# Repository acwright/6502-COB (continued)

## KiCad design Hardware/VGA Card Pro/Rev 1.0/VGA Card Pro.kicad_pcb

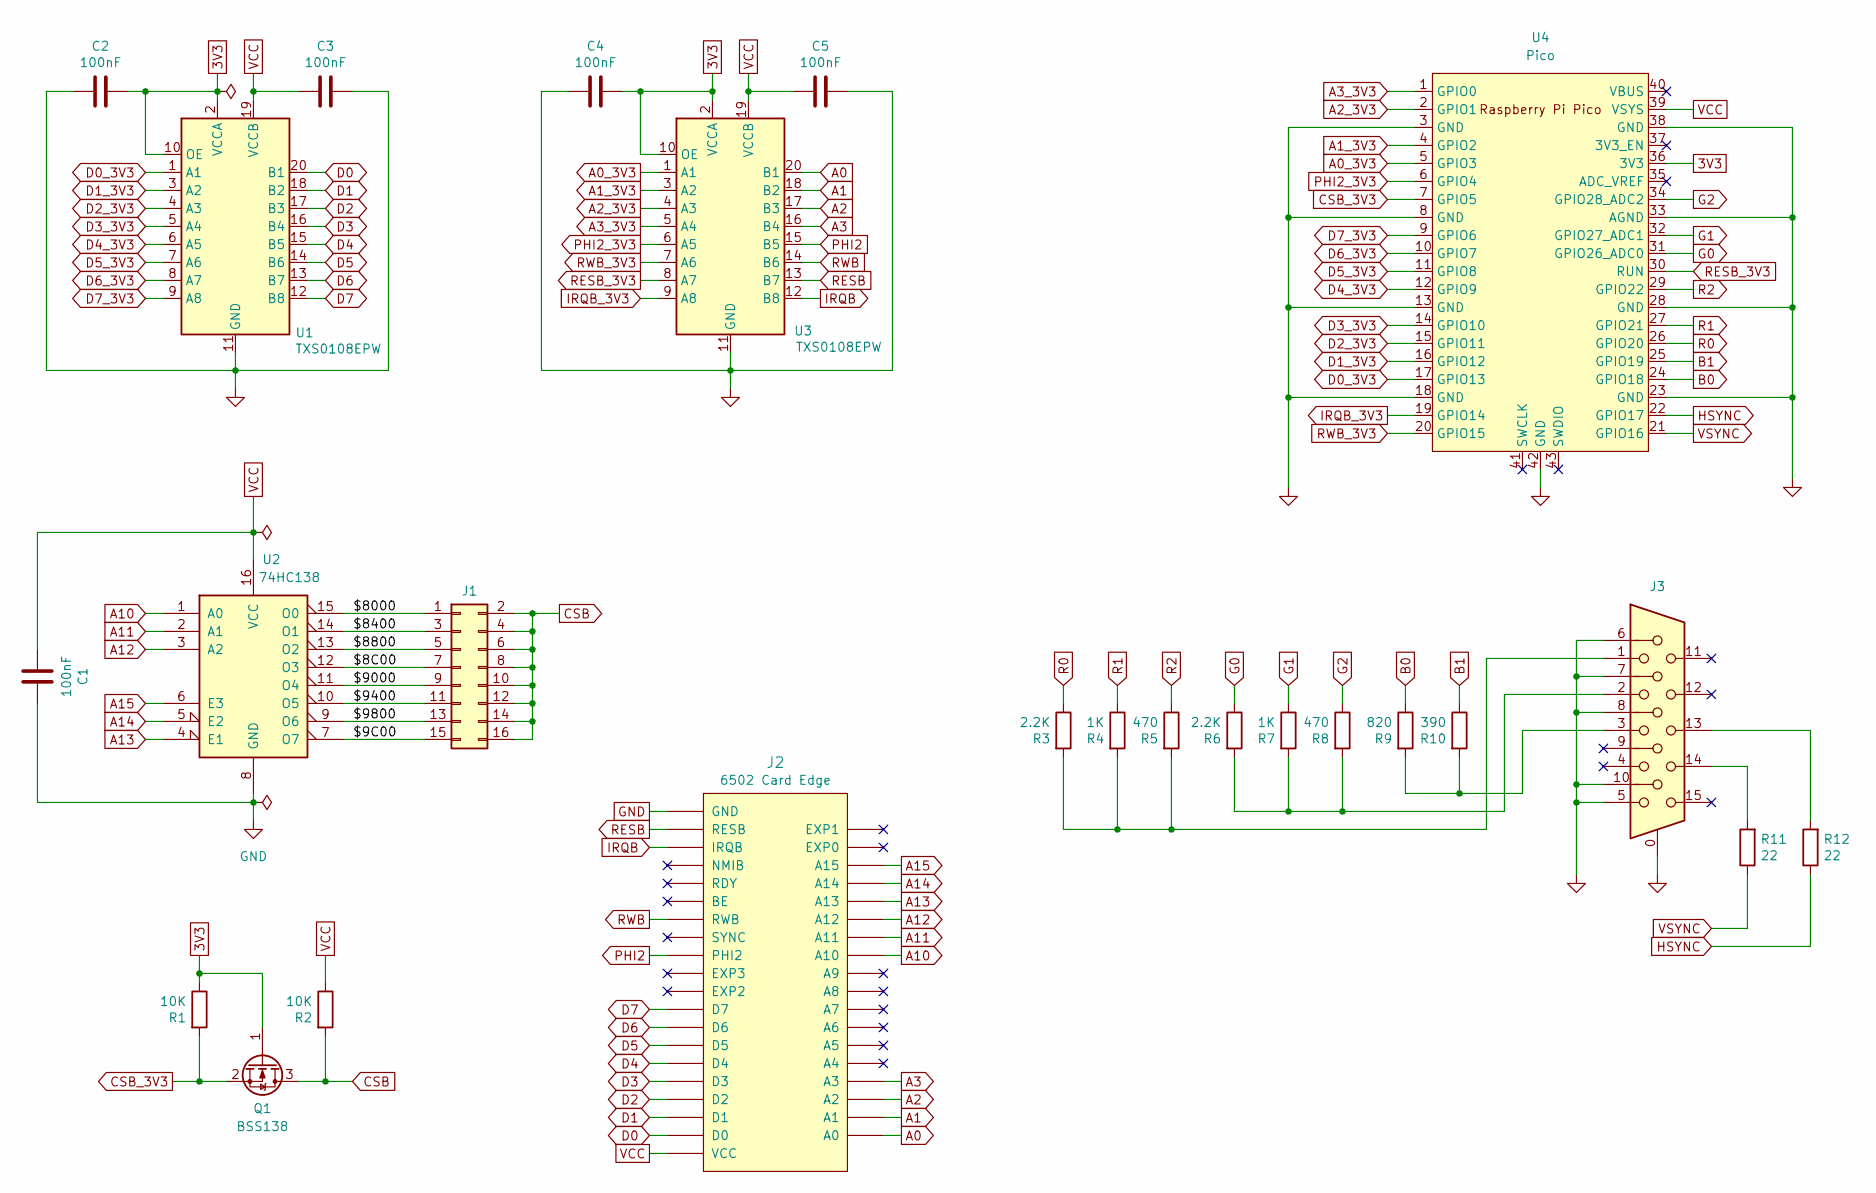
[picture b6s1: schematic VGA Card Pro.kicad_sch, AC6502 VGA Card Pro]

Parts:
C1, C2, C3, C4, C5: 100nF; C_0805_2012Metric; LCSC C49678
J1: Conn_02x08_Odd_Even; PinHeader_2x08_P2.54mm_Vertical; Digikey S2011EC-40-ND
J2: 6502 Card Edge
J3: DE15_Receptacle_HighDensity_MountingHoles; DSUB-15-HD_Female_Horizontal_P2.29x1.98mm_EdgePinOffset3.03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; Digikey 609-5181-ND
Q1: BSS138; SOT-23; LCSC C78284
R1, R2: 10K; R_0805_2012Metric; LCSC C17414
R3, R6: 2.2K; R_0805_2012Metric; LCSC C17520
R4, R7: 1K; R_0805_2012Metric; LCSC C17513
R5, R8: 470; R_0805_2012Metric; LCSC C17710
R9: 820; R_0805_2012Metric; LCSC C17837
R10: 390; R_0805_2012Metric; LCSC C17655
R11, R12: 22; R_0805_2012Metric; LCSC C17561
U1, U3: TXS0108EPW; TSSOP-20_4.4x6.5mm_P0.65mm; LCSC C17206
U2: 74HC138; SOIC-16_3.9x9.9mm_P1.27mm; LCSC C5602
U4: Pico; Raspberry Pi Pico; Digikey 2648-SC0915CT-ND

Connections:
3V3: C2.1, C4.1, Q1.1 (G), R1.1, U1.2 (VCCA), U1.10 (OE), U3.2 (VCCA), U3.10 (OE), U4.36 (3V3)
/$8C00: J1.7, U2.12 (O3)
/$9C00: J1.15, U2.7 (O7)
/$8000: J1.1, U2.15 (O0)
/$8400: J1.3, U2.14 (O1)
/$8800: J1.5, U2.13 (O2)
/$9000: J1.9, U2.11 (O4)
/$9400: J1.11, U2.10 (O5)
/$9800: J1.13, U2.9 (O6)
A0: J2.A0, U3.20 (B1)
A0_3V3: U3.1 (A1), U4.5 (GPIO3)
A1: J2.A1, U3.18 (B2)
A1_3V3: U3.3 (A2), U4.4 (GPIO2)
A2: J2.A2, U3.17 (B3)
A2_3V3: U3.4 (A3), U4.2 (GPIO1)
A3: J2.A3, U3.16 (B4)
A3_3V3: U3.5 (A4), U4.1 (GPIO0)
A10: J2.A10, U2.1 (A0)
A11: J2.A11, U2.2 (A1)
A12: J2.A12, U2.3 (A2)
A13: J2.A13, U2.4 (E1)
A14: J2.A14, U2.5 (E2)
A15: J2.A15, U2.6 (E3)
B0: R9.1, U4.24 (GPIO18)
B1: R10.1, U4.25 (GPIO19)
CSB: J1.2, J1.4, J1.6, J1.8, J1.10, J1.12, J1.14, J1.16, Q1.3 (D), R2.2
CSB_3V3: Q1.2 (S), R1.2, U4.7 (GPIO5)
D0: J2.D0, U1.20 (B1)
D0_3V3: U1.1 (A1), U4.17 (GPIO13)
D1: J2.D1, U1.18 (B2)
D1_3V3: U1.3 (A2), U4.16 (GPIO12)
D2: J2.D2, U1.17 (B3)
D2_3V3: U1.4 (A3), U4.15 (GPIO11)
D3: J2.D3, U1.16 (B4)
D3_3V3: U1.5 (A4), U4.14 (GPIO10)
D4: J2.D4, U1.15 (B5)
D4_3V3: U1.6 (A5), U4.12 (GPIO9)
D5: J2.D5, U1.14 (B6)
D5_3V3: U1.7 (A6), U4.11 (GPIO8)
D6: J2.D6, U1.13 (B7)
D6_3V3: U1.8 (A7), U4.10 (GPIO7)
D7: J2.D7, U1.12 (B8)
D7_3V3: U1.9 (A8), U4.9 (GPIO6)
G0: R6.1, U4.31 (GPIO26_ADC0)
G1: R7.1, U4.32 (GPIO27_ADC1)
G2: R8.1, U4.34 (GPIO28_ADC2)
GND: C1.2, C2.2, C3.1, C4.2, C5.1, J2.GND, J3.0, J3.5, J3.6, J3.7, J3.8, J3.10, U1.11 (GND), U2.8 (GND), U3.11 (GND), U4.3 (GND), U4.8 (GND), U4.13 (GND), U4.18 (GND), U4.23 (GND), U4.28 (GND), U4.33 (AGND), U4.38 (GND), U4.42 (GND)
HSYNC: R12.1, U4.22 (GPIO17)
IRQB: J2.IRQB, U3.12 (B8)
IRQB_3V3: U3.9 (A8), U4.19 (GPIO14)
unnamed: J3.1, R3.2, R4.2, R5.2
unnamed: J3.2, R6.2, R7.2, R8.2
unnamed: J3.3, R9.2, R10.2
unnamed: J3.13, R12.2
unnamed: J3.14, R11.2
PHI2: J2.PHI2, U3.15 (B5)
PHI2_3V3: U3.6 (A5), U4.6 (GPIO4)
R0: R3.1, U4.26 (GPIO20)
R1: R4.1, U4.27 (GPIO21)
R2: R5.1, U4.29 (GPIO22)
RESB: J2.RESB, U3.13 (B7)
RESB_3V3: U3.8 (A7), U4.30 (RUN)
RWB: J2.RWB, U3.14 (B6)
RWB_3V3: U3.7 (A6), U4.20 (GPIO15)
VCC: C1.1, C3.2, C5.2, J2.VCC, R2.1, U1.19 (VCCB), U2.16 (VCC), U3.19 (VCCB), U4.39 (VSYS)
VSYNC: R11.1, U4.21 (GPIO16)

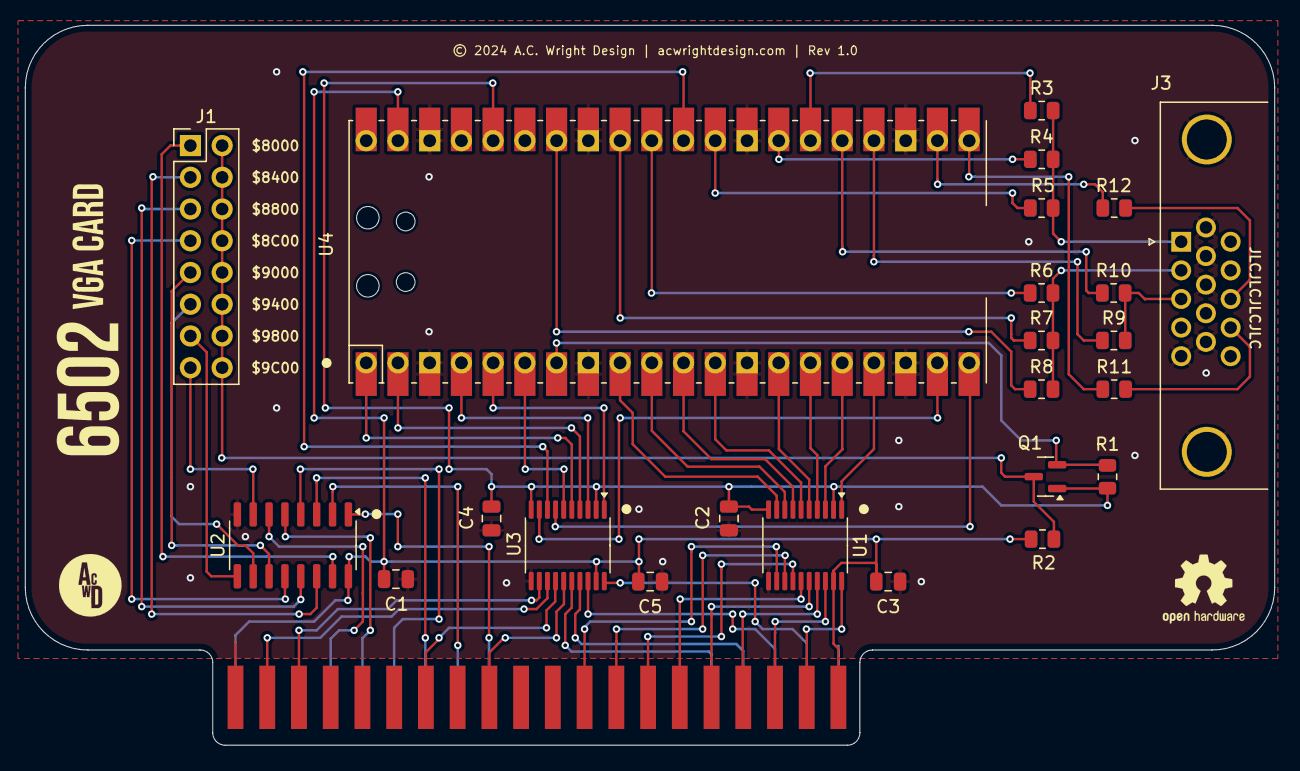
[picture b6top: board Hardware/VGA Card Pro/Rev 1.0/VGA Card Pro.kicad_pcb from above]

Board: 2 copper layers, 100.0 x 57.6 mm, 25 parts (0 on the bottom side), 66 nets.

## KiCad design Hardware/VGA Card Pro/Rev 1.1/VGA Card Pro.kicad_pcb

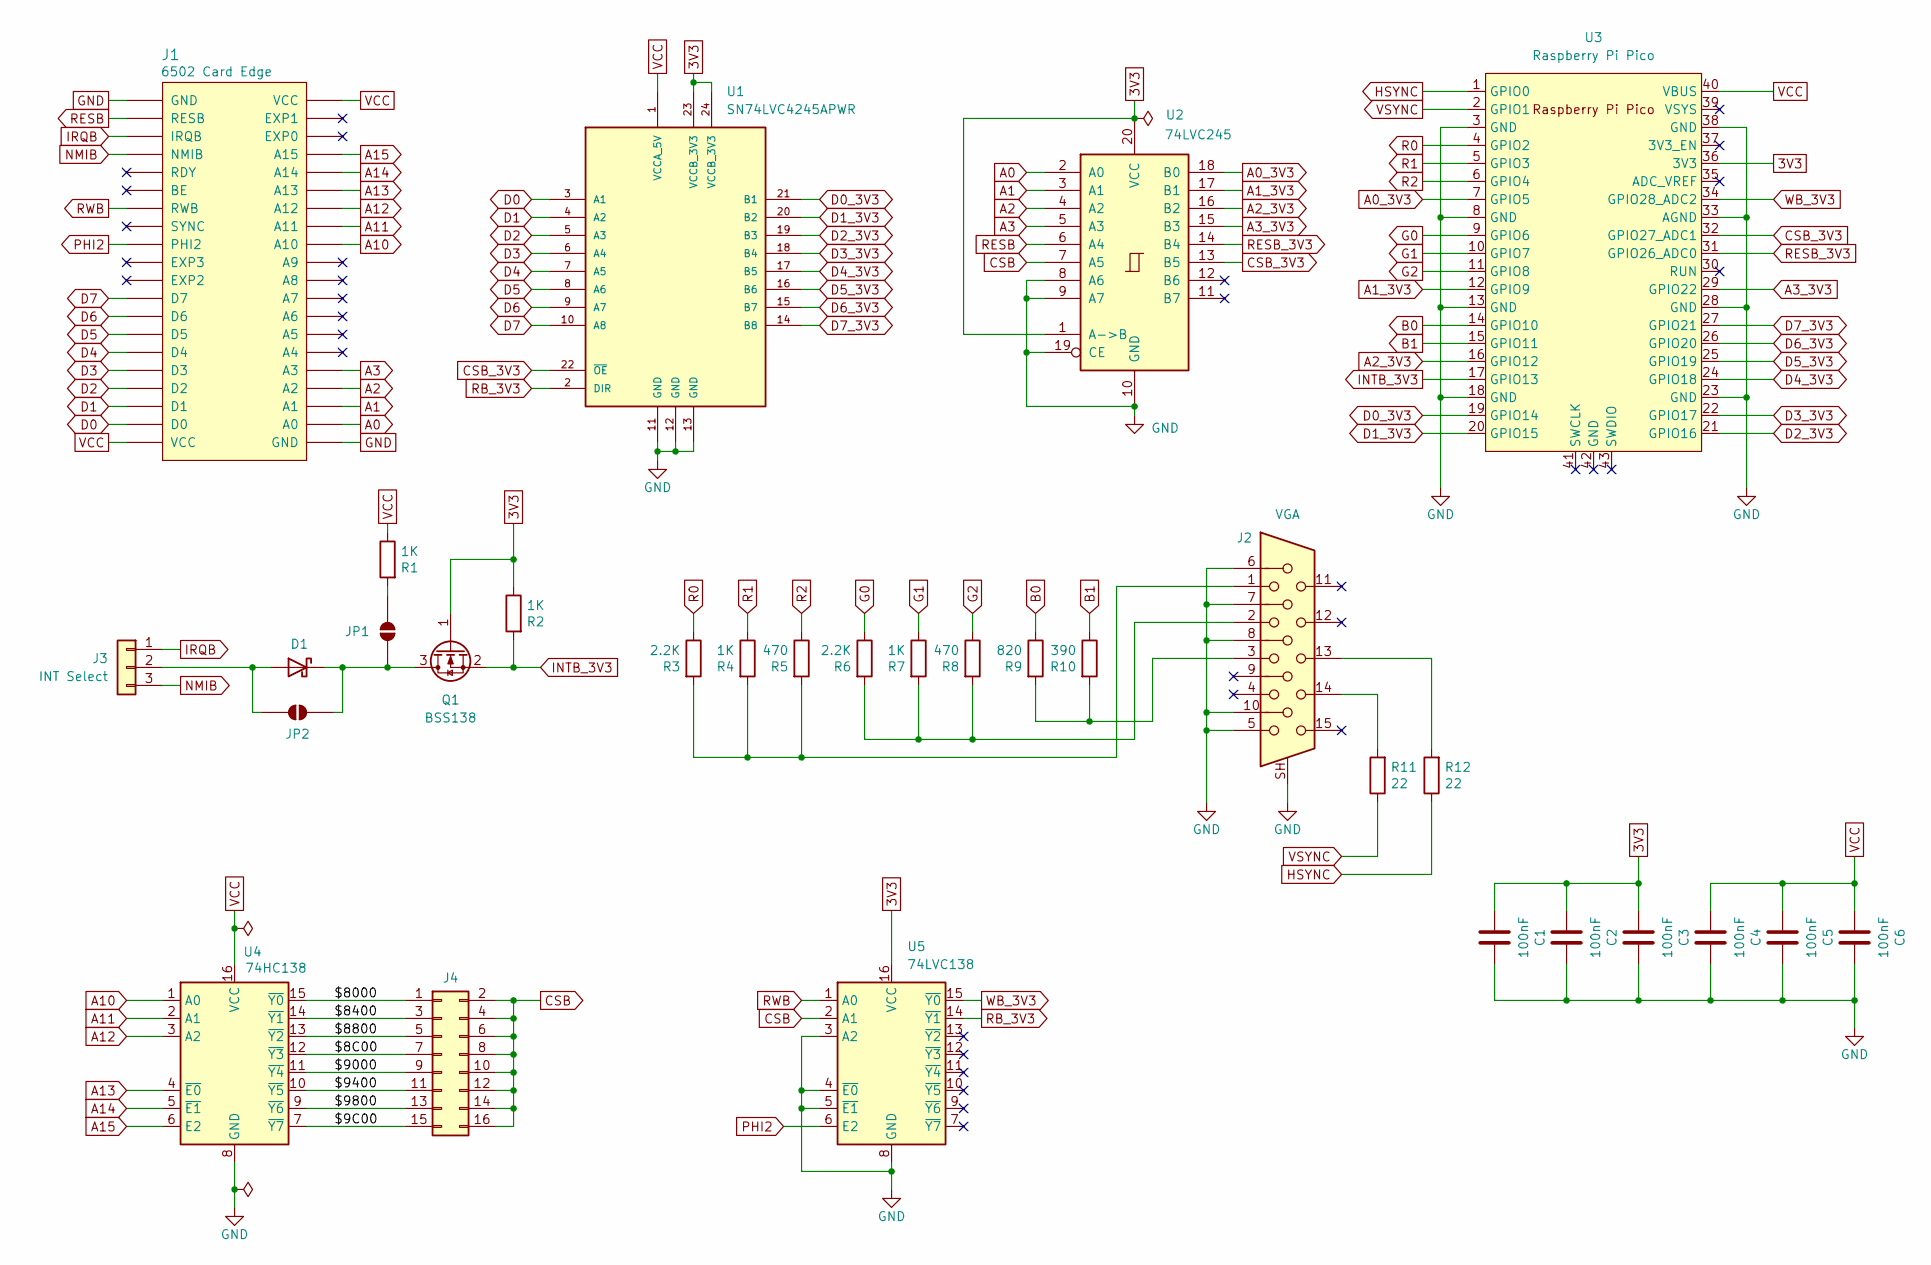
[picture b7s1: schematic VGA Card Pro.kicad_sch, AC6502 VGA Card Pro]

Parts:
C1, C2, C3, C4, C5, C6: 100nF; C_0805_2012Metric; LCSC C49678
D1: BAT85; D_DO-35_SOD27_P7.62mm_Horizontal; Digikey BAT85SCT-ND
J1: 6502 Card Edge
J2: VGA; DSUB-15-HD_Socket_Horizontal_P2.29x1.90mm_EdgePinOffset3.03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; Digikey 609-5181-ND
J3: INT Select; PinHeader_1x03_P2.54mm_Vertical; Digikey S1011EC-40-ND
J4: Conn_02x08_Odd_Even; PinHeader_2x08_P2.54mm_Vertical; Digikey S2011EC-40-ND
JP1, JP2: SolderJumper_2_Open; SolderJumper-2_P1.3mm_Open_RoundedPad1.0x1.5mm
Q1: BSS138; SOT-23; LCSC C78284
R1, R2, R4, R7: 1K; R_0805_2012Metric; LCSC C17513
R3, R6: 2.2K; R_0805_2012Metric; LCSC C17520
R5, R8: 470; R_0805_2012Metric; LCSC C17710
R9: 820; R_0805_2012Metric; LCSC C17837
R10: 390; R_0805_2012Metric; LCSC C17655
R11, R12: 22; R_0805_2012Metric; LCSC C17561
U1: SN74LVC4245APWR; TSSOP-24_4.4x7.8mm_P0.65mm; LCSC C7859
U2: 74LVC245; TSSOP-20_4.4x6.5mm_P0.65mm; LCSC C6082
U3: Raspberry Pi Pico; Digikey 2648-SC0915CT-ND
U4: 74HC138; SOIC-16_3.9x9.9mm_P1.27mm; LCSC C5602
U5: 74LVC138; SOIC-16_3.9x9.9mm_P1.27mm; LCSC C6061

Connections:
3V3: C1.1, C2.1, C3.1, Q1.1 (G), R2.1, U1.23 (VCCB_3V3), U1.24 (VCCB_3V3), U2.1 (A->B), U2.20 (VCC), U3.36 (3V3), U5.16 (VCC)
/$8C00: J4.7, U4.12 (~Y3)
/$9C00: J4.15, U4.7 (~Y7)
/$8000: J4.1, U4.15 (~Y0)
/$8400: J4.3, U4.14 (~Y1)
/$8800: J4.5, U4.13 (~Y2)
/$9000: J4.9, U4.11 (~Y4)
/$9400: J4.11, U4.10 (~Y5)
/$9800: J4.13, U4.9 (~Y6)
A0: J1.A0, U2.2 (A0)
A0_3V3: U2.18 (B0), U3.7 (GPIO5)
A1: J1.A1, U2.3 (A1)
A1_3V3: U2.17 (B1), U3.12 (GPIO9)
A2: J1.A2, U2.4 (A2)
A2_3V3: U2.16 (B2), U3.16 (GPIO12)
A3: J1.A3, U2.5 (A3)
A3_3V3: U2.15 (B3), U3.29 (GPIO22)
A10: J1.A10, U4.1 (A0)
A11: J1.A11, U4.2 (A1)
A12: J1.A12, U4.3 (A2)
A13: J1.A13, U4.4 (~E0)
A14: J1.A14, U4.5 (~E1)
A15: J1.A15, U4.6 (E2)
B0: R9.1, U3.14 (GPIO10)
B1: R10.1, U3.15 (GPIO11)
CSB: J4.2, J4.4, J4.6, J4.8, J4.10, J4.12, J4.14, J4.16, U2.7 (A5), U5.2 (A1)
CSB_3V3: U1.22 (~OE), U2.13 (B5), U3.32 (GPIO27_ADC1)
D0: J1.D0, U1.3 (A1)
D0_3V3: U1.21 (B1), U3.19 (GPIO14)
D1: J1.D1, U1.4 (A2)
D1_3V3: U1.20 (B2), U3.20 (GPIO15)
D2: J1.D2, U1.5 (A3)
D2_3V3: U1.19 (B3), U3.21 (GPIO16)
D3: J1.D3, U1.6 (A4)
D3_3V3: U1.18 (B4), U3.22 (GPIO17)
D4: J1.D4, U1.7 (A5)
D4_3V3: U1.17 (B5), U3.24 (GPIO18)
D5: J1.D5, U1.8 (A6)
D5_3V3: U1.16 (B6), U3.25 (GPIO19)
D6: J1.D6, U1.9 (A7)
D6_3V3: U1.15 (B7), U3.26 (GPIO20)
D7: J1.D7, U1.10 (A8)
D7_3V3: U1.14 (B8), U3.27 (GPIO21)
G0: R6.1, U3.9 (GPIO6)
G1: R7.1, U3.10 (GPIO7)
G2: R8.1, U3.11 (GPIO8)
GND: C1.2, C2.2, C3.2, C4.2, C5.2, C6.2, J1.GND, J2.5, J2.6, J2.7, J2.8, J2.10, J2.SH, U1.11 (GND), U1.12 (GND), U1.13 (GND), U2.8 (A6), U2.9 (A7), U2.10 (GND), U2.19 (CE), U3.3 (GND), U3.8 (GND), U3.13 (GND), U3.18 (GND), U3.23 (GND), U3.28 (GND), U3.33 (AGND), U3.38 (GND), U4.8 (GND), U5.3 (A2), U5.4 (~E0), U5.5 (~E1), U5.8 (GND)
HSYNC: R12.1, U3.1 (GPIO0)
INTB_3V3: Q1.2 (S), R2.2, U3.17 (GPIO13)
IRQB: J1.IRQB, J3.1
NMIB: J1.NMIB, J3.3
unnamed: D1.2 (A), J3.2, JP2.2 (B)
unnamed: D1.1 (K), JP1.2 (B), JP2.1 (A), Q1.3 (D)
unnamed: J2.1, R3.2, R4.2, R5.2
unnamed: J2.2, R6.2, R7.2, R8.2
unnamed: J2.3, R9.2, R10.2
unnamed: J2.13, R12.2
unnamed: J2.14, R11.2
unnamed: JP1.1 (A), R1.2
PHI2: J1.PHI2, U5.6 (E2)
R0: R3.1, U3.4 (GPIO2)
R1: R4.1, U3.5 (GPIO3)
R2: R5.1, U3.6 (GPIO4)
RB_3V3: U1.2 (DIR), U5.14 (~Y1)
RESB: J1.RESB, U2.6 (A4)
RESB_3V3: U2.14 (B4), U3.31 (GPIO26_ADC0)
RWB: J1.RWB, U5.1 (A0)
VCC: C4.1, C5.1, C6.1, J1.VCC, R1.1, U1.1 (VCCA_5V), U3.40 (VBUS), U4.16 (VCC)
VSYNC: R11.1, U3.2 (GPIO1)
WB_3V3: U3.34 (GPIO28_ADC2), U5.15 (~Y0)

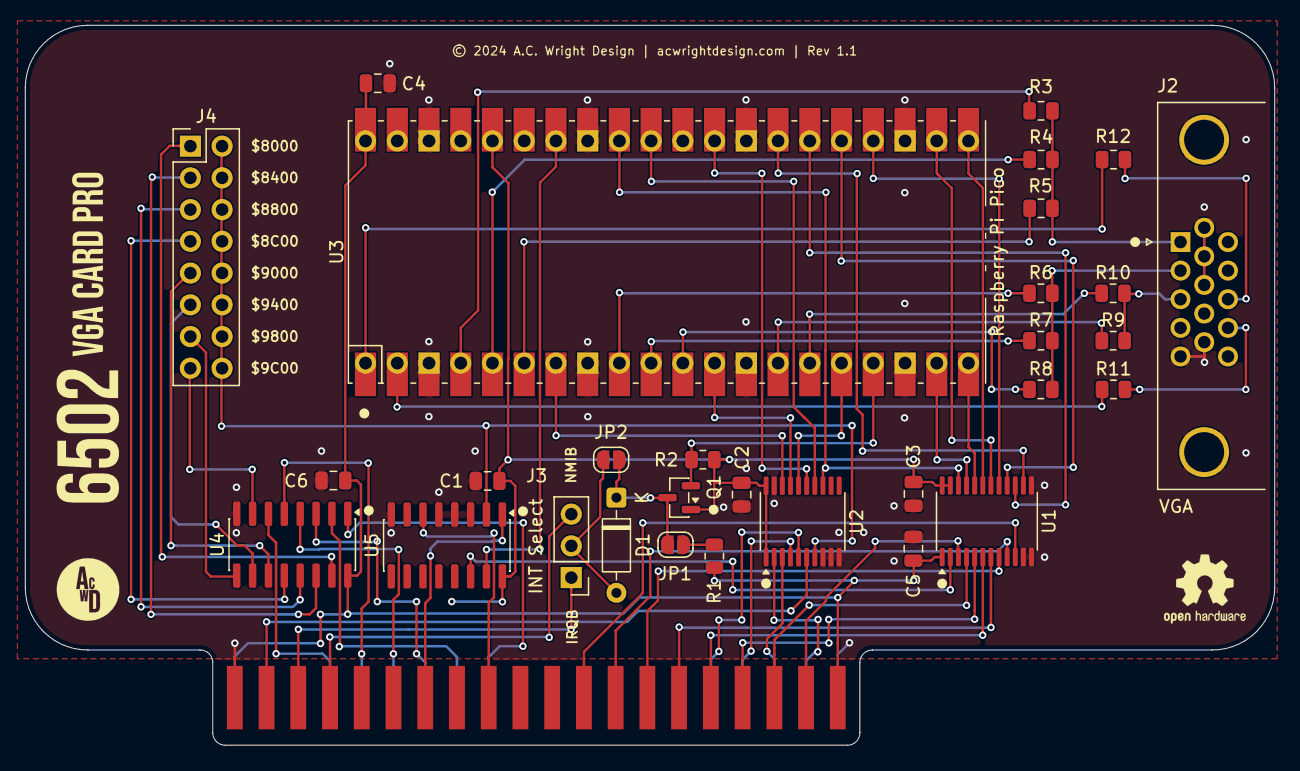
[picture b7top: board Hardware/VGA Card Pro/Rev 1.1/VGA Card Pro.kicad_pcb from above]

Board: 2 copper layers, 100.0 x 57.6 mm, 31 parts (0 on the bottom side), 70 nets.
